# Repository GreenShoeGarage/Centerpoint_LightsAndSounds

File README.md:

# Centerpoint Lights and Sounds

| RP2040 Pin | Keypad PCB Header Row (J) | Keypad PCB Header Pin (P) | Pin Function                                                    |
|------------|---------------------------|---------------------------|-----------------------------------------------------------------|
| D2         | J1                        | 5                         | Keypad Column for Button 9                                      |
| D3         | J1                        | 6                         | Keypad Column for Buttons 10, 11, 12, 13                        |
| D4         | J1                        | 7                         | Keypad Column for Buttons 1,2,3,4                               |
| D5         | J1                        | 8                         | Keypad Column for Buttons 5, 6, 7, 8                            |
| D6         | J2                        | 1                         | Keypad Row for Buttons 5, 6, 7, 8, 9                            |
| D7         | J2                        | 3                         |  Button 1 LED GND   AND GREEN LED GROUND                        |
| D8         | J2                        | 5                         |  Button 2 LED GND   AND YELLOW LED GROUND                       |
| D9         | J2                        | 7                         |  GND for RED LED         AND MAYBE  Button 3 LED GND****        |
| D10        | J2                        | 11                        | Keypad Row for Buttons 1,2,3,4,10,11,12,13                      |
| D11        | SW                        | BLACK                     | VCC for Switch                                                  |
| D12        | J2                        | 4                         | Buttons 8 and 13 LED GND                                        |
| D12        | J2                        | 6                         | Buttons 5 and 10 LED GND                                        |
| D12        | J2                        | 8                         | Buttons 6 and 11 LED GND                                        |
| D12        | J2                        | 9                         | Buttons 4 and 9 LED GND                                         |
| D12        | J2                        | 10                        | Buttons 7 and 12 LED GND                                        |
| D13        | SW                        | RED                       | Switch Position 2                                               |
| VCC        | J2                        | 2                         | Top Row of Rubber Buttons (1-8) LED Vcc                         |
| VCC        | J2                        | 13                        | Bottom Row of Rubber Buttons (9-13) LED Vcc   AND  GYR LEDs Vcc |
| A0         | J1                        | 1                         | Buttons 1 and 5 and 10                                          |
| A1         | J1                        | 2                         | Buttons 2 and 6 and 11                                          |
| A2         | J1                        | 3                         |  Buttons 3 and 7 and 12                                         |
| A3         | J1                        | 4                         |  Buttons 4 and 8 and 9 and 13                                   |
| A4         | unassigned                | unassigned                | Reserved for I2C                                                |
| A5         | unassigned                | unassigned                | Reserved for I2C                                                |
| A6         | SW                        | GREEN                     | Switch Position 1                                               |
| A7         | SW                        | WHITE                     | Switch Position 3                                               |

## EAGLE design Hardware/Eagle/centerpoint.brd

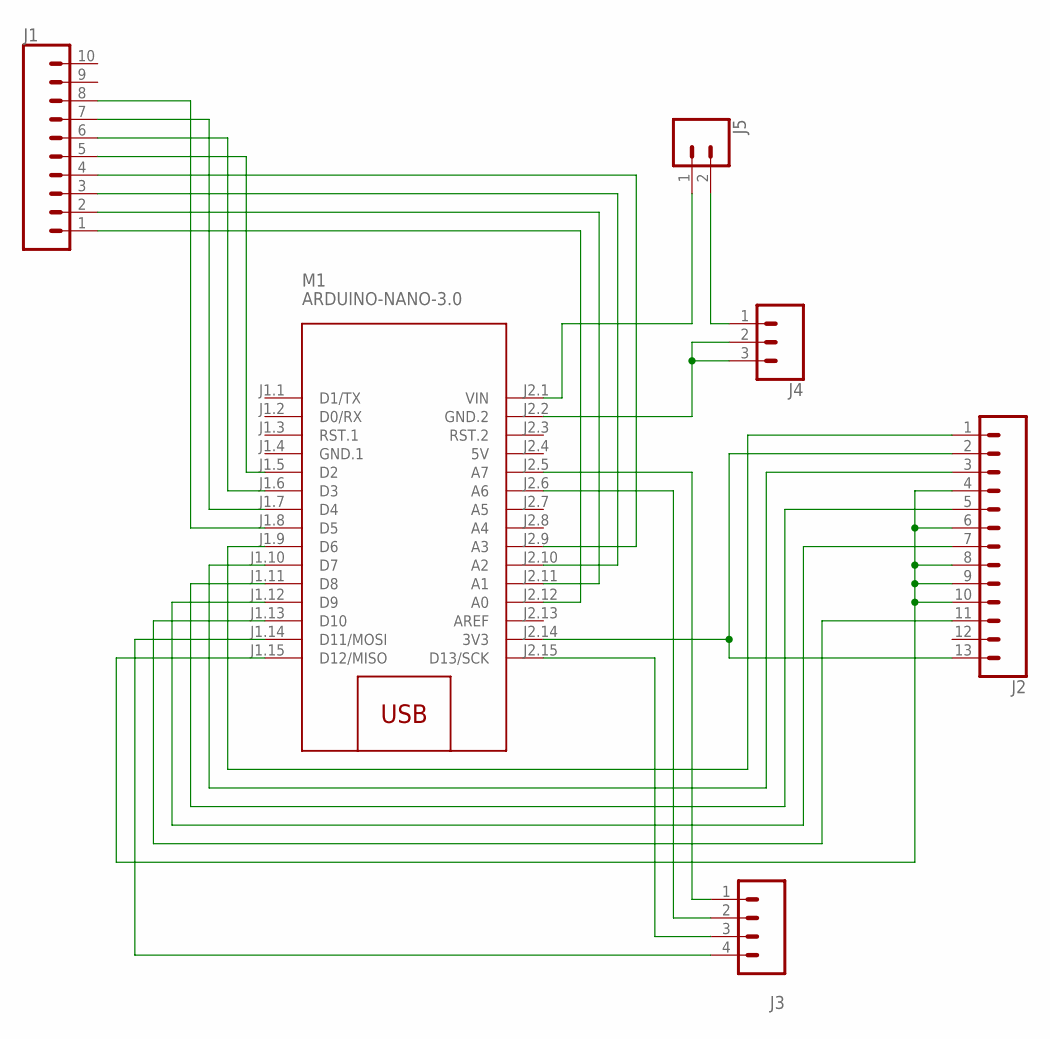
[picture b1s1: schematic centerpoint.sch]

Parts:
J1: CONN_10"; 1X10
J2: CONN_13; 1X13
J3: CONN_04PTH; 1X04
J4: CONN_03-SCREW-5MM; SCREWTERMINAL-5MM-3
J5: CONN_023.5MM; SCREWTERMINAL-3.5MM-2
M1: ARDUINO-NANO-3.0

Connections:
5V: M1.J2.4 (5V)
GND.1: M1.J1.4 (GND.1)
unnamed: J1.5, M1.J1.5 (D2)
unnamed: J1.6, M1.J1.6 (D3)
unnamed: J1.7, M1.J1.7 (D4)
unnamed: J1.8, M1.J1.8 (D5)
unnamed: J2.1, M1.J1.9 (D6)
unnamed: J2.3, M1.J1.10 (D7)
unnamed: J2.5, M1.J1.11 (D8)
unnamed: J2.7, M1.J1.12 (D9)
unnamed: J2.11, M1.J1.13 (D10)
unnamed: J3.4, M1.J1.14 (D11/MOSI)
unnamed: J2.4, J2.6, J2.8, J2.9, J2.10, M1.J1.15 (D12/MISO)
unnamed: J2.2, J2.13, M1.J2.14 (3V3)
unnamed: J1.1, M1.J2.12 (A0)
unnamed: J1.2, M1.J2.11 (A1)
unnamed: J1.3, M1.J2.10 (A2)
unnamed: J1.4, M1.J2.9 (A3)
unnamed: J3.1, M1.J2.5 (A7)
unnamed: J3.2, M1.J2.6 (A6)
unnamed: J3.3, M1.J2.15 (D13/SCK)
unnamed: J4.2, J4.3, M1.J2.2 (GND.2)
unnamed: J5.1, M1.J2.1 (VIN)
unnamed: J4.1, J5.2

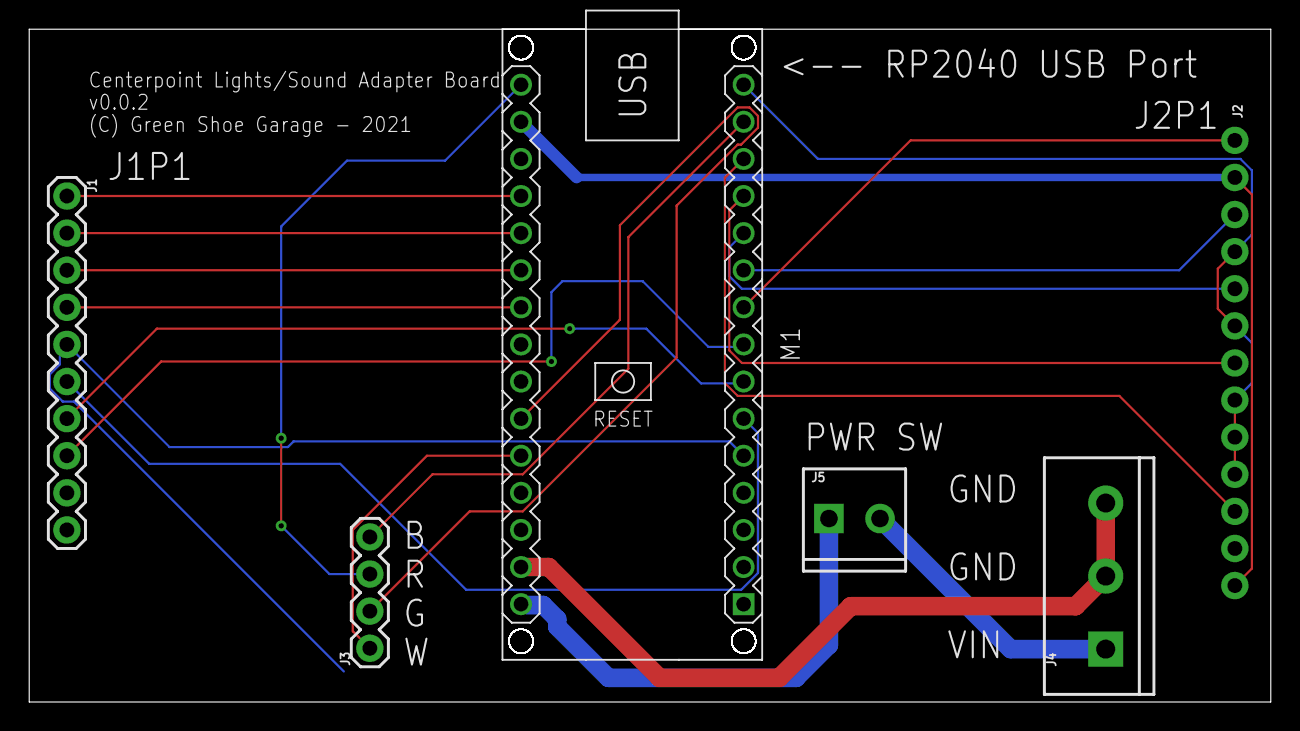
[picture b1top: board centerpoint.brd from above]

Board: 2 copper layers, 85.0 x 46.1 mm, 6 parts (1 on the bottom side), 22 nets.

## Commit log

2021-09-09 init commit
2021-09-16 baseline functionality achieved for all buttons and switch positions
2021-09-16 init BRD and SCH commit for interface board
2021-09-16 added system architecture docs
2021-09-17 Added PCB docs
2021-09-17 Adjusted Switch pin assignments
2021-09-17 updated adapter board PCB layout
2021-09-17 corrected placement of GND screw terminal and switch interface header
2021-09-17 revised images based on v0.0.2 of PCB
2021-09-17 comment out AnalogRead for A6 and A7 for troubleshooting
2021-09-18 added to silkscreen, change from 2.54 to 5mm screw terminal
2021-09-19 print the MAC address of central device
2021-09-19 minor code cleanup
2021-09-19 reworked board layout
2021-09-22 added power switch and screw terminal for battery (VIN)
2021-09-23 detect individual button presses in RPi Python script

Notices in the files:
parts and their libraries:
SparkFun-Connectors: Licensing: Creative Commons ShareAlike 4.0 International - https://creativecommons.org/licenses/by-sa/4.0
diy-modules: Released under the Creative Commons Attribution 4.0 International License: http://creativecommons.org/licenses/by/4.0
